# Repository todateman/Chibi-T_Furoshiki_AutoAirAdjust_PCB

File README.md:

# Chibi-T_Furoshiki_AutoAirAdjust_PCB

M5Stack Basic / Core2 用の空気圧自動調整コントローラー基板の KiCad プロジェクトです。  
1次側・2次側の空気圧センサと燃圧センサの値を M5Stack で監視し、ソレノイドバルブの開閉によって
1次側から2次側への圧縮空気の流れを自動制御します。

## 概要

- 対応ホスト: M5Stack Basic / Core2（MBUS 30pin コネクタで直結するスタック型基板）
- センサ入力
  - 1次側・2次側 空気圧センサ：[DFRobot Gravity MPX5700AP (SEN0456)](https://wiki.dfrobot.com/sen0456/docs/18937) × 2 個
    （センサ自体はアナログ出力のため、 I2C ADC モジュール経由で Grove I2C バスに接続）
  - 燃圧センサ：0–1.0 MPa / 0.5–4.5V アナログ出力タイプ 1 個
    （基板上の 12bit ADC（ADS1015）で読み取り）
- アクチュエータ出力：DC12Vソレノイドバルブ 1 系統（1次側→2次側の圧縮空気の開閉弁を GPIO トリガーで駆動）
- 電源：車両/バッテリーの 12V 入力から基板上の降圧コンバータで 5V を生成し、 M5Stack と各センサへ供給

## システム構成

```mermaid
flowchart TD
    J2["J2: from_12V_Power\n+12V入力"]
    F1["F1 ポリスイッチ\n(リセッタブルヒューズ)"]
    VBUS["VBUS\n保護後の12V系"]
    U1["U1 MP1584EN\n降圧DC/DCコンバータ\n12V → 5V"]
    V5["5V 系統"]
    J1["J1 M-BUS (30pin)\nM5Stack本体へ"]
    J3["J3 from_5V_Power\n外部5V供給/分岐用テストポイント"]
    J4["J4 PRESSURE_SEN\n燃圧センサ入力"]
    R10["R10 100kΩ\nAIN0 プルダウン\n(断線検出用)"]
    U2["U2 ADS1015\n12bit I2C ADC\nI2Cアドレス 0x48\nAIN0 = 燃圧センサ信号"]
    I2C["I2Cバス\nSDA/SCL\nM5Stack GPIO21/22"]
    J5["J5 Grove I2C\n外部I2C ADC経由\nGravity MPX5700AP #1\n(1次側空気圧センサ)"]
    J6["J6 Grove I2C\n外部I2C ADC経由\nGravity MPX5700AP #2\n(2次側空気圧センサ)"]
    Q1["Q1 AO3400A\nNchMOSFET\nローサイドスイッチ"]
    SOL_TRG["SOL_TRG\nM5Stack GPIO"]
    J7["J7 SOLENOID\nソレノイドバルブ(+)"]

    J2 --> F1 --> VBUS
    VBUS --> U1 --> V5
    VBUS --> J7
    VBUS --> Q1
    SOL_TRG -->|ゲート制御| Q1
    Q1 -->|スイッチング| GND

    V5 --> J1
    V5 --> J3
    V5 --> J4

    J4 --> U2
    R10 -.->|GND プルダウン| U2
    U2 --> I2C
    I2C --> J5
    I2C --> J6
```

## 主な機能

1. **空気圧計測（1次側・2次側）**
   Gravity MPX5700AP を 2 個、I2C ADC モジュール経由で Grove I2C コネクタ（J5・J6）に接続し、
   M5Stack の I2C バス上で読み取ります。  

   **2026.08.07 更新 Ver1.02**: M5Stack Basic / Core2 の I2C バスのピン配置は以下の通りです。

   | ボード | SDA | SCL |
   | --- | --- | --- |
   | M5Stack Basic | GPIO02 | GPIO05 |
   | M5Core2 | GPIO32 | GPIO33 |

   DFRobot Gravity MPX5700AP (SEN0456) のモジュール上の DIP スイッチで、I2Cアドレスは `0x16` 〜 `0x19` のいずれかに設定可能です。

2. **燃圧計測**
   0–1.0 MPa（0.5–4.5V 出力）のアナログ燃圧センサを J4（PRESSURE_SEN）に接続し、
   基板上の ADS1015（12bit I2C ADC、U2）の AIN0 チャンネルで読み取ります。  
   ADS1015 の ADDR ピンは GND に接続されており、I2C アドレスは `0x48` 固定です。

   **2026.08.15 更新 Ver1.03**: AIN0 ネット（J4 ピン2 ～ U2 AIN0 間）に R10（100kΩ、GNDプルダウン）を追加しました。  
   センサ本体は 0.5–4.5V 出力（0V付近には振れない）のため、J4 のセンサ配線が断線するとプルダウンにより AIN0 が 0V 付近まで下がり、ファームウェア側で「正常なセンサレンジ（≒0.5–4.5V相当のADC値）を下回っている＝断線」と判定できます。  
   R10 は 0603 サイズ・100kΩ（R2/R4 と同一部品、LCSC C25803）で、センサの低インピーダンス出力への影響はごく僅かです。  
   なお、ADS1015 の電源電圧は 3.3V（絶対最大定格 AIN ≦ VDD+0.3V ≒ 3.6V）である一方、センサ最大出力は 4.5V のため、現状の直結構成では正常動作範囲内でも ADC の絶対最大定格を超える可能性があります。  
   今回のプルダウン抵抗はこの問題を解決するものではなく、別途分圧抵抗などによるレベルシフトの検討が必要です。  
   （本リビジョンでは未対応）

3. **ソレノイドバルブ制御**
   1次側から2次側への圧縮空気の通路を開閉するソレノイドバルブを、M5Stack の GPIO（M5Stack: GPIO13 / Core2: GPIO19）, SOL_TRG）からのトリガー信号で駆動します。  
   GPIO → ゲート抵抗 R8(1kΩ) → Q1(AO3400A, NchMOSFET) のローサイドスイッチ構成で、R9(12kΩ) がゲートのプルダウン（起動時の誤動作防止）、D2(1N4148WS) が逆起電力吸収用フライホイールダイオードです。  
   **ソレノイドバルブの電源は VBUS（保護後の12V系統）から供給されます。**  
   **2026.07.14 更新 Ver1.01**: GPIO34は入力専用のため、ソレノイド駆動用のGPIOはGPIO13に変更しました。

4. **電源生成**
   J2（from_12V_Power）から入力した車両/バッテリー電源は、F1（ポリスイッチ／リセッタブルヒューズ）で保護された後、U1（MP1584EN-LF-Z 降圧 DC/DC コンバータ）で 5V に変換されます。  
   5V は J1（M-BUS）経由で M5Stack 本体、および J4 の燃圧センサ電源として供給されます。  
   3.3V 系統は M5Stack 本体（MBUS 経由）からの供給を利用しており、基板上では ADS1015 の電源および I2C プルアップ抵抗（R6, R7）に使われます。  
   J3（from_5V_Power）は外部への5V供給、または分岐出力を取り出すためのテストポイント/コネクタです。

## コネクタ一覧

| 番号 | 名称 | 種類 | 用途 |
| --- | --- | --- | --- |
| J1 | M-BUS | 2x15 (30pin) | M5Stack Basic/Core2 本体との直結用バスコネクタ |
| J2 | from_12V_Power | JST XH 1x02 | 車両/バッテリーからの 12V 電源入力 |
| J3 | from_5V_Power | Conn 1x02 | 外部 5V 供給／分岐出力用テストポイント |
| J4 | PRESSURE_SEN | JST XH 1x03 | 燃圧センサ入力（+5V／信号(AIN0)／GND、R10でGNDプルダウンし断線検出） |
| J5 | I2C | Grove 4pin | 外部I2C ADC経由で空気圧センサ(Gravity MPX5700AP)を接続 |
| J6 | I2C | Grove 4pin | 外部I2C ADC経由で空気圧センサ(Gravity MPX5700AP)を接続 |
| J7 | SOLENOID | JST XH 1x02 | ソレノイドバルブ駆動出力（VBUS系統をQ1でスイッチ） |

## 主要部品（抜粋）

| 部品番号 | 部品 | 役割 |
| --- | --- | --- |
| U1 | MP1584EN-LF-Z | 降圧DC/DCコンバータ（12V→5V、L1/R1/R3で出力電圧設定） |
| U2 | ADS1015IDGS | 12bit I2C ADC（燃圧センサ読み取り、I2Cアドレス 0x48） |
| Q1 | AO3400A | NchMOSFET（ソレノイドバルブのローサイドスイッチ） |
| D1 | Schottky | 電源保護用ダイオード |
| D2 | 1N4148WS | ソレノイドコイルのフライホイールダイオード |
| F1 | Polyfuse (Polyfuse_Small) | 12V入力のリセッタブルヒューズ |
| L1 | 10uH | 降圧コンバータのインダクタ |
| R10 | 100k (0603) | AIN0（J4燃圧センサ信号）のGNDプルダウン。センサ断線検出用 |

部品表全体は [`production/bom.csv`](production/bom.csv) を参照してください。

## 基板仕様

- 基板サイズ：約 50.05mm × 50.05mm x 1.0mm
- 層数：2層（F.Cu / B.Cu）
- マウントホール：M3 × 4（H1–H4）、M2 × 4（H5–H8）
- KiCad バージョン：KiCad 8 系フォーマット

## ディレクトリ構成

```txt
├── Chibi-T_Furoshiki_AutoAirAdjust_PCB.kicad_pro   # プロジェクトファイル
├── Chibi-T_Furoshiki_AutoAirAdjust_PCB.kicad_sch    # 回路図
├── Chibi-T_Furoshiki_AutoAirAdjust_PCB.kicad_pcb    # 基板データ
├── C15051/                                          # MP1584EN 用シンボルライブラリ
├── OPL_Connector.lib / OPL_Connector.pretty/         # コネクタ用シンボル・フットプリントライブラリ
├── logos.pretty/                                    # 基板ロゴ用フットプリント
├── production/                                       # 製造用出力データ（ガーバー一式・BOM・部品配置等）
├── Chibi-T_Furoshiki_AutoAirAdjust_PCB-backups/      # KiCad 自動バックアップ（zip）
└── LICENSE.txt                                       # ライセンス（MIT）
```

## 製造データ

`production/` フォルダに、製造発注用のデータ一式が出力済みです。

- `Chibi-T_Furoshiki_AutoAirAdjust_PCB.zip` … ガーバー等一式
- `bom.csv` … 部品表
- `positions.csv` … 部品実装位置データ（ピックアンドプレース）
- `designators.csv` … 部品番号リスト
- `netlist.ipc` … IPC ネットリスト

## ファームウェア

M5Stack 側の制御プログラム（センサ読み取り・ソレノイド制御ロジック）は本リポジトリには含まれません。
別リポジトリで管理しています。

## ライセンス

MIT License（詳細は [`LICENSE.txt`](LICENSE.txt) を参照）

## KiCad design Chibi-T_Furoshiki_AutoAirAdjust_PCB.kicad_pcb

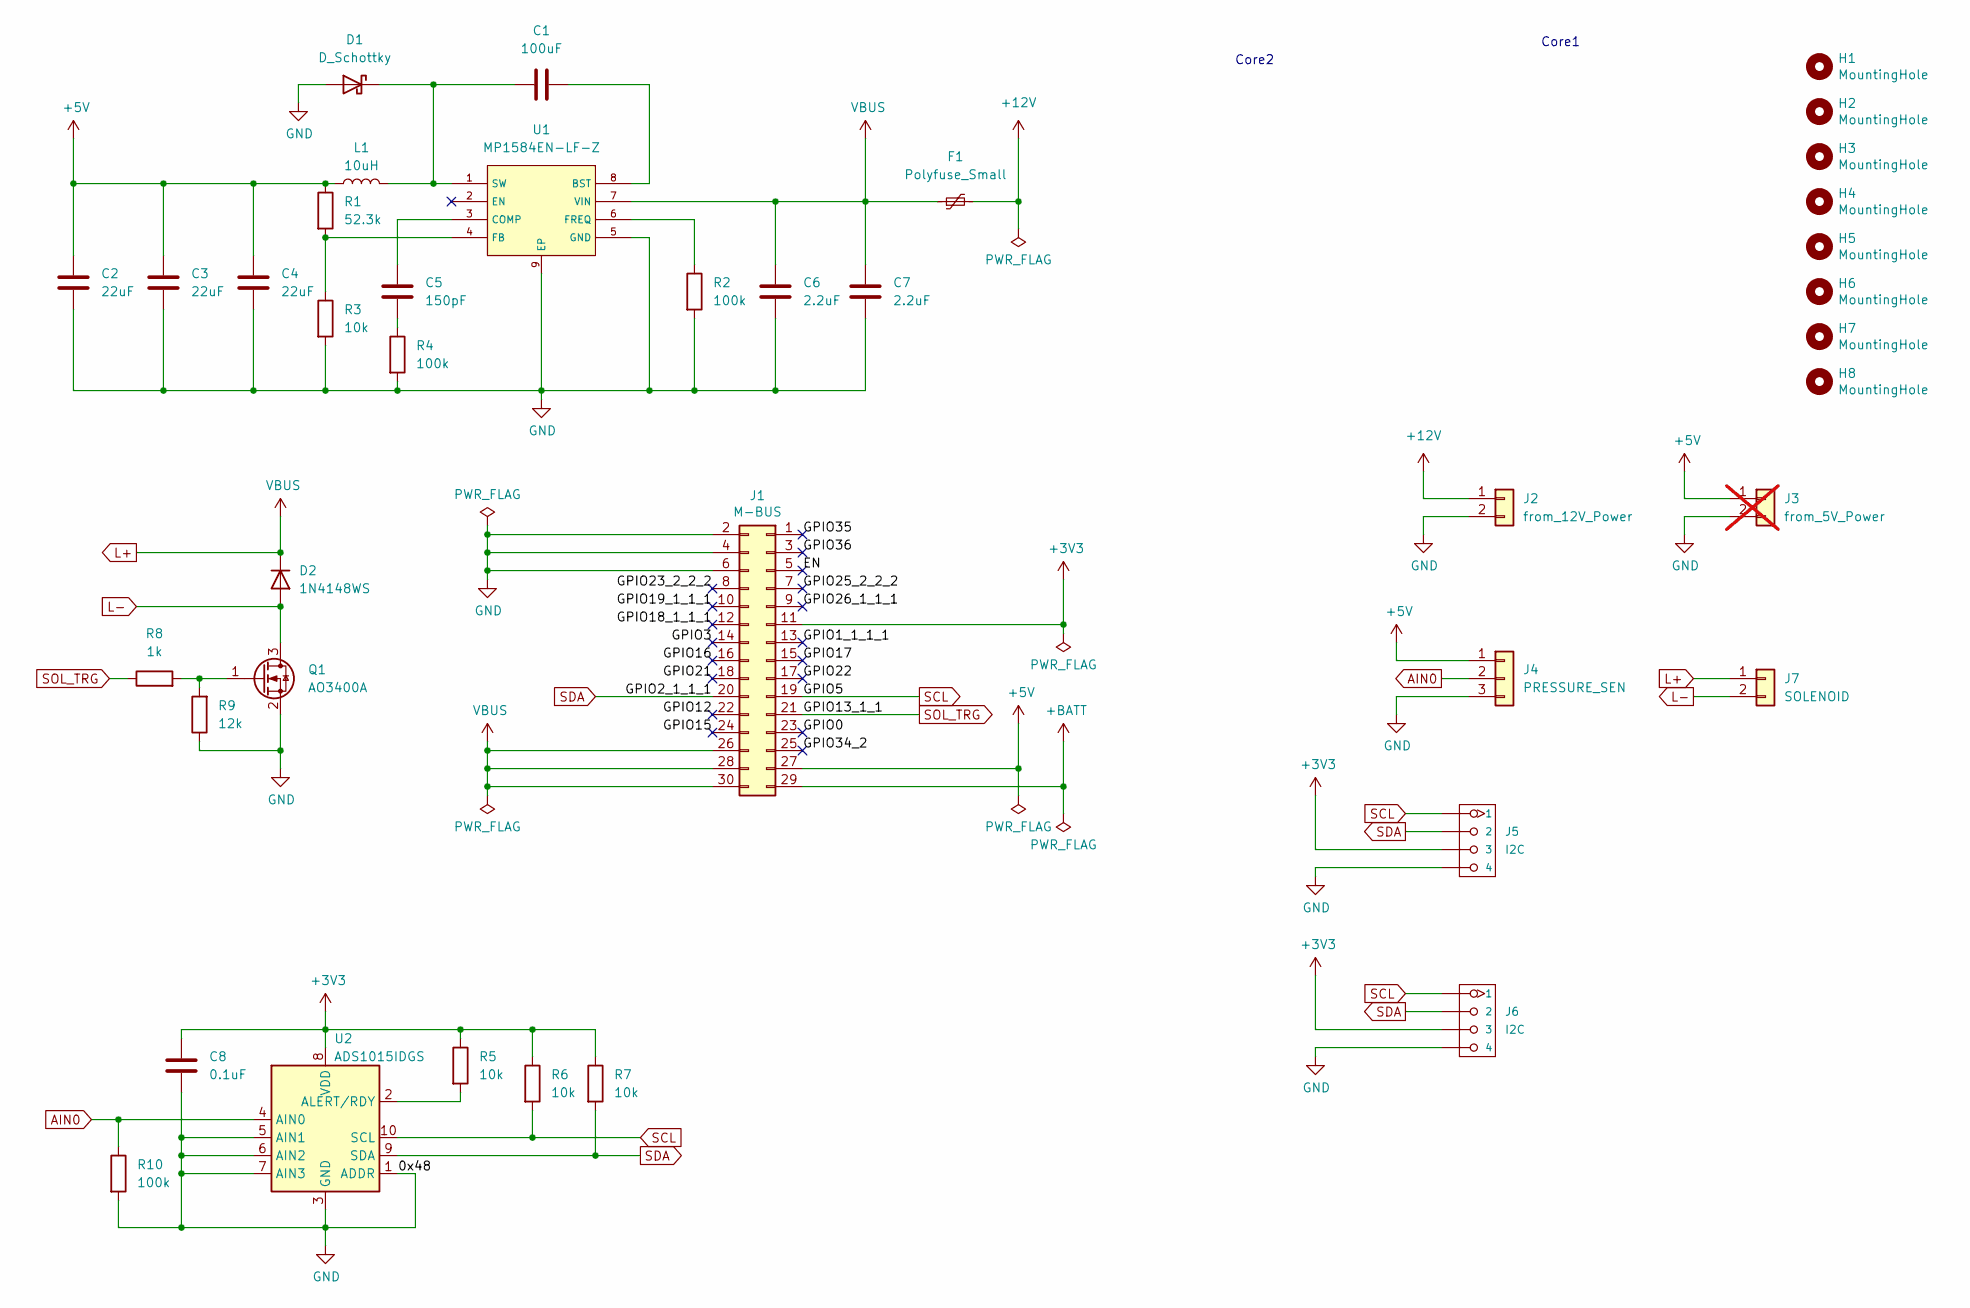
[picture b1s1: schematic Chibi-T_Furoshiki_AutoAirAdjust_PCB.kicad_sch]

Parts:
C1: 100uF; C_1206_3216Metric; LCSC C15008
C2, C3, C4: 22uF; C_0603_1608Metric; LCSC C59461
C5: 150pF; C_0603_1608Metric; LCSC C1594
C6, C7: 2.2uF; C_0805_2012Metric; LCSC C377773
C8: 0.1uF; C_0402_1005Metric; LCSC C1525
D1: D_Schottky; D_SMA; LCSC C22452
D2: 1N4148WS; D_SOD-323; LCSC C2128
F1: Polyfuse_Small; Fuse_1812_4532Metric; LCSC C1884489
H1, H2, H3, H4: MountingHole; BF@MountingHole_3.2mm_M3
H5, H6, H7, H8: MountingHole; BF@MountingHole_2.2mm_M2
J1: M-BUS; BF@M5Stack_MBUS
J2: from_12V_Power; JST_XH_S2B-XH-A_1x02_P2.50mm_Horizontal
J3: from_5V_Power; PinSocket_1x02_P2.54mm_Vertical; not fitted
J4: PRESSURE_SEN; JST_XH_S3B-XH-A_1x03_P2.50mm_Horizontal
J5, J6: I2C; GROVE-HW4-2.0-90D
J7: SOLENOID; JST_XH_S2B-XH-A_1x02_P2.50mm_Horizontal
L1: 10uH; L_Sunlord_SWPA3015S; LCSC C45403
Q1: AO3400A; SOT-23; LCSC C20917
R1: 52.3k; R_0603_1608Metric; LCSC C23198
R2, R4, R10: 100k; R_0603_1608Metric; LCSC C25803
R3, R5, R6, R7: 10k; R_0805_2012Metric; LCSC C17414
R8: 1k; R_0805_2012Metric; LCSC C17513
R9: 12k; R_0805_2012Metric; LCSC C17444
U1: MP1584EN-LF-Z; SOIC-8_L5.0-W4.0-P1.27-LS6.0-BL-EP2.0; Manufacturer Part MP1584EN-LF-Z; LCSC C15051
U2: ADS1015IDGS; TSSOP-10_3x3mm_P0.5mm; LCSC C193969

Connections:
/EN: J1.5
/EN_1: J1.5
/EN_2: J1.5
/GPIO0: J1.23
/GPIO0_1: J1.23
/GPIO0_2: J1.23
/GPIO1_1_1_1: J1.13
/GPIO1_1_1_1_1: J1.13
/GPIO1_1_1_1_2: J1.13
/GPIO3: J1.14
/GPIO3_1: J1.14
/GPIO3_2: J1.14
/GPIO12: J1.22
/GPIO12_1: J1.22
/GPIO12_2: J1.22
/GPIO15: J1.24
/GPIO15_1: J1.24
/GPIO15_2: J1.24
/GPIO16: J1.16
/GPIO16_1: J1.16
/GPIO16_2: J1.16
/GPIO17: J1.15
/GPIO17_1: J1.15
/GPIO17_2: J1.15
/GPIO18_1_1_1: J1.12
/GPIO18_1_1_1_1: J1.12
/GPIO18_1_1_1_2: J1.12
/GPIO19_1_1_1: J1.10
/GPIO19_1_1_1_1: J1.10
/GPIO19_1_1_1_2: J1.10
/GPIO21: J1.18
/GPIO21_1: J1.18
/GPIO21_2: J1.18
/GPIO22: J1.17
/GPIO22_1: J1.17
/GPIO22_2: J1.17
/GPIO23_2_2_2: J1.8
/GPIO23_2_2_2_1: J1.8
/GPIO23_2_2_2_2: J1.8
/GPIO25_2_2_2: J1.7
/GPIO25_2_2_2_1: J1.7
/GPIO25_2_2_2_2: J1.7
/GPIO26_1_1_1: J1.9
/GPIO26_1_1_1_1: J1.9
/GPIO26_1_1_1_2: J1.9
/GPIO34_2: J1.25
/GPIO34_2_1: J1.25
/GPIO34_2_2: J1.25
/GPIO35: J1.1
/GPIO35_1: J1.1
/GPIO35_2: J1.1
/GPIO36: J1.3
/GPIO36_1: J1.3
/GPIO36_2: J1.3
AIN0: J4.2, R10.1, U2.4 (AIN0)
L-: D2.2 (A), J7.2, Q1.3 (D)
unnamed: C5.1, R4.1
unnamed: C1.1, D1.1 (K), L1.2, U1.1 (SW)
unnamed: Q1.1 (G), R8.2, R9.2
unnamed: C1.2, U1.8 (BST)
unnamed: C5.2, U1.3 (COMP)
unnamed: R1.2, R3.1, U1.4 (FB)
unnamed: R2.1, U1.6 (FREQ)
unnamed: R5.2, U2.2 (ALERT/RDY)
SCL: J1.19, J5.1, J6.1, R6.2, U2.10 (SCL)
SDA: J1.20, J5.2, J6.2, R7.2, U2.9 (SDA)
SOL_TRG: J1.21, R8.1

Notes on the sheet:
Core1
Core2

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
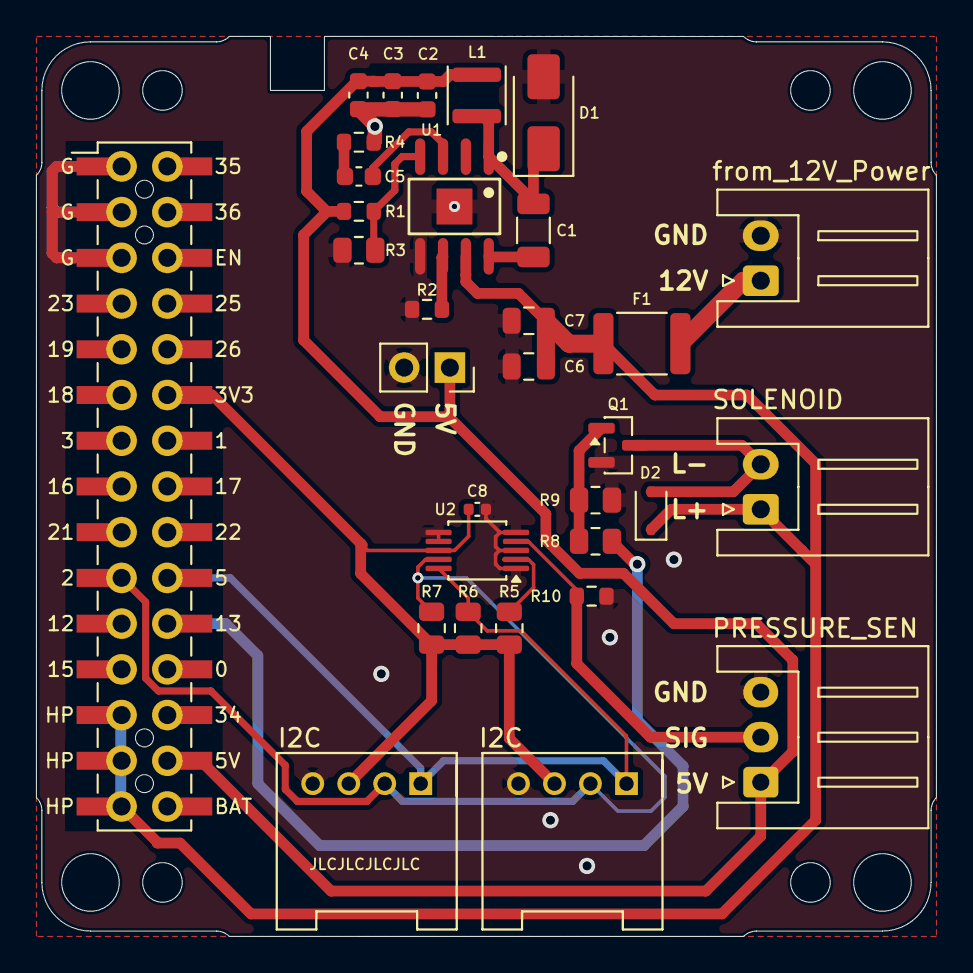
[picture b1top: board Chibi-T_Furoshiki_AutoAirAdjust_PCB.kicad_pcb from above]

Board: 2 copper layers, 50.0 x 50.0 mm, 40 parts (0 on the bottom side), 18 nets.

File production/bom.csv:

Designator,Footprint,Quantity,Value,LCSC Part #
C1,1206,1,100uF,C15008
"C2, C3, C4",0603,3,22uF,C59461
C5,0603,1,150pF,C1594
"C6, C7",0805,2,2.2uF,C377773
C8,0402,1,0.1uF,C1525
D1,D_SMA,1,D_Schottky,C22452
D2,D_SOD-323,1,1N4148WS,C2128
F1,1812,1,Polyfuse_Small,C1884489
"H1, H2, H3, H4",BF@MountingHole_3.2mm_M3,4,MountingHole,
"H5, H6, H7, H8",BF@MountingHole_2.2mm_M2,4,MountingHole,
J1,BF@M5Stack_MBUS,1,M-BUS,
J2,JST_XH_S2B-XH-A_1x02_P2.50mm_Horizontal,1,from_12V_Power,
J4,JST_XH_S3B-XH-A_1x03_P2.50mm_Horizontal,1,PRESSURE_SEN,
J6,GROVE-HW4-2.0-90D,1,I2C,
J7,JST_XH_S2B-XH-A_1x02_P2.50mm_Horizontal,1,SOLENOID,
L1,L_Sunlord_SWPA3015S,1,10uH,C45403
Q1,SOT-23,1,AO3400A,C20917
R1,0603,1,52.3k,C23198
"R10, R2, R4",0603,3,100k,C25803
"R3, R5, R6, R7",0805,4,10k,C17414
R8,0805,1,1k,C17513
R9,0805,1,12k,C17444
U1,SOIC-8_L5.0-W4.0-P1.27-LS6.0-BL-EP2.0,1,MP1584EN-LF-Z,C15051
U2,TSSOP-10_3x3mm_P0.5mm,1,ADS1015IDGS,C193969
